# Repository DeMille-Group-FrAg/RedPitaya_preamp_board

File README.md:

Schematics for a simple amplifier pcb to step Red Pitaya output voltage from 0--1V or 0--2V up to 0--5V (or other gain, if so desired). See the documentation section in https://github.com/DeMille-Group-FrAg/TransferInterferometer.

Designed by John Dewhurst in February 2023 for FrAg.

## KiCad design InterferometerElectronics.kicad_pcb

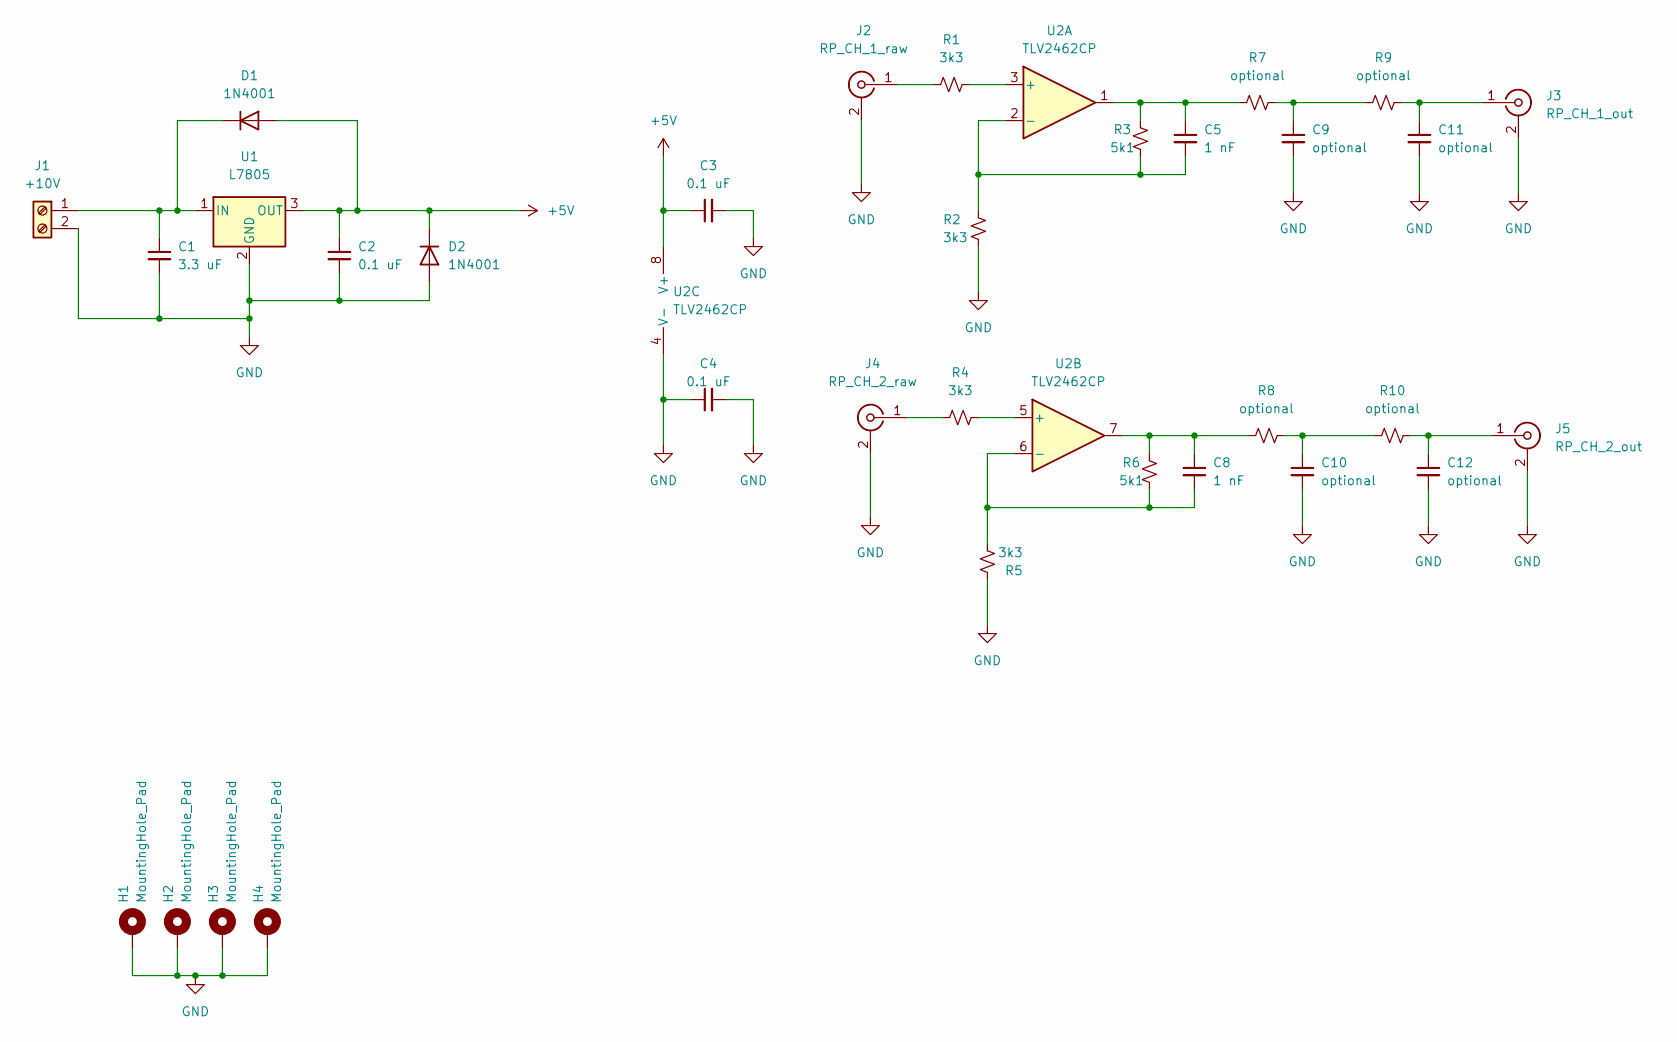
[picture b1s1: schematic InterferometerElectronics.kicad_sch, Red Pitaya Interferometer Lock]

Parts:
C1: 3.3 uF; C_Disc_D7.5mm_W5.0mm_P7.50mm
C2, C3, C4: 0.1 uF; C_Disc_D7.5mm_W5.0mm_P7.50mm
C5, C8: 1 nF; C_Disc_D7.5mm_W5.0mm_P7.50mm
C9, C10, C11, C12: optional; C_Disc_D7.5mm_W5.0mm_P7.50mm
D1, D2: 1N4001; D_DO-41_SOD81_P10.16mm_Horizontal
H1, H2, H3, H4: MountingHole_Pad; MountingHole_3mm_Pad_Via
J1: +10V; PhoenixContact_MCV_1,5_2-G-5.08_1x02_P5.08mm_Vertical
J2: RP_CH_1_raw; SMA_Amphenol_132134-16_Vertical
J3: RP_CH_1_out; SMA_Amphenol_132134-16_Vertical
J4: RP_CH_2_raw; SMA_Amphenol_132134-16_Vertical
J5: RP_CH_2_out; SMA_Amphenol_132134-16_Vertical
R1, R2, R4, R5: 3k3; R_Axial_DIN0207_L6.3mm_D2.5mm_P10.16mm_Horizontal
R3, R6: 5k1; R_Axial_DIN0207_L6.3mm_D2.5mm_P10.16mm_Horizontal
R7, R8, R9, R10: optional; R_Axial_DIN0207_L6.3mm_D2.5mm_P10.16mm_Horizontal
U1: L7805; TO-220-3_Horizontal_TabDown
U2: TLV2462CP; DIP-8_W7.62mm_Socket

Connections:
+5V: C2.1, C3.1, D1.2 (A), D2.1 (K), U1.3 (OUT), U2.8 (V+)
GND: C1.2, C2.2, C3.2, C4.1, C4.2, C9.2, C10.2, C11.2, C12.2, D2.2 (A), H1.1, H2.1, H3.1, H4.1, J1.2, J2.2 (Ext), J3.2 (Ext), J4.2 (Ext), J5.2 (Ext), R2.2, R5.1, U1.2 (GND), U2.4 (V-)
unnamed: C1.1, D1.1 (K), J1.1, U1.1 (IN)
unnamed: C5.1, R3.1, R7.1, U2.1
unnamed: C5.2, R2.1, R3.2, U2.2 (-)
unnamed: C8.1, R6.1, R8.1, U2.7
unnamed: C8.2, R5.2, R6.2, U2.6 (-)
unnamed: C9.1, R7.2, R9.1
unnamed: C10.1, R8.2, R10.1
unnamed: C11.1, J3.1 (In), R9.2
unnamed: C12.1, J5.1 (In), R10.2
unnamed: J2.1 (In), R1.1
unnamed: J4.1 (In), R4.1
unnamed: R1.2, U2.3 (+)
unnamed: R4.2, U2.5 (+)

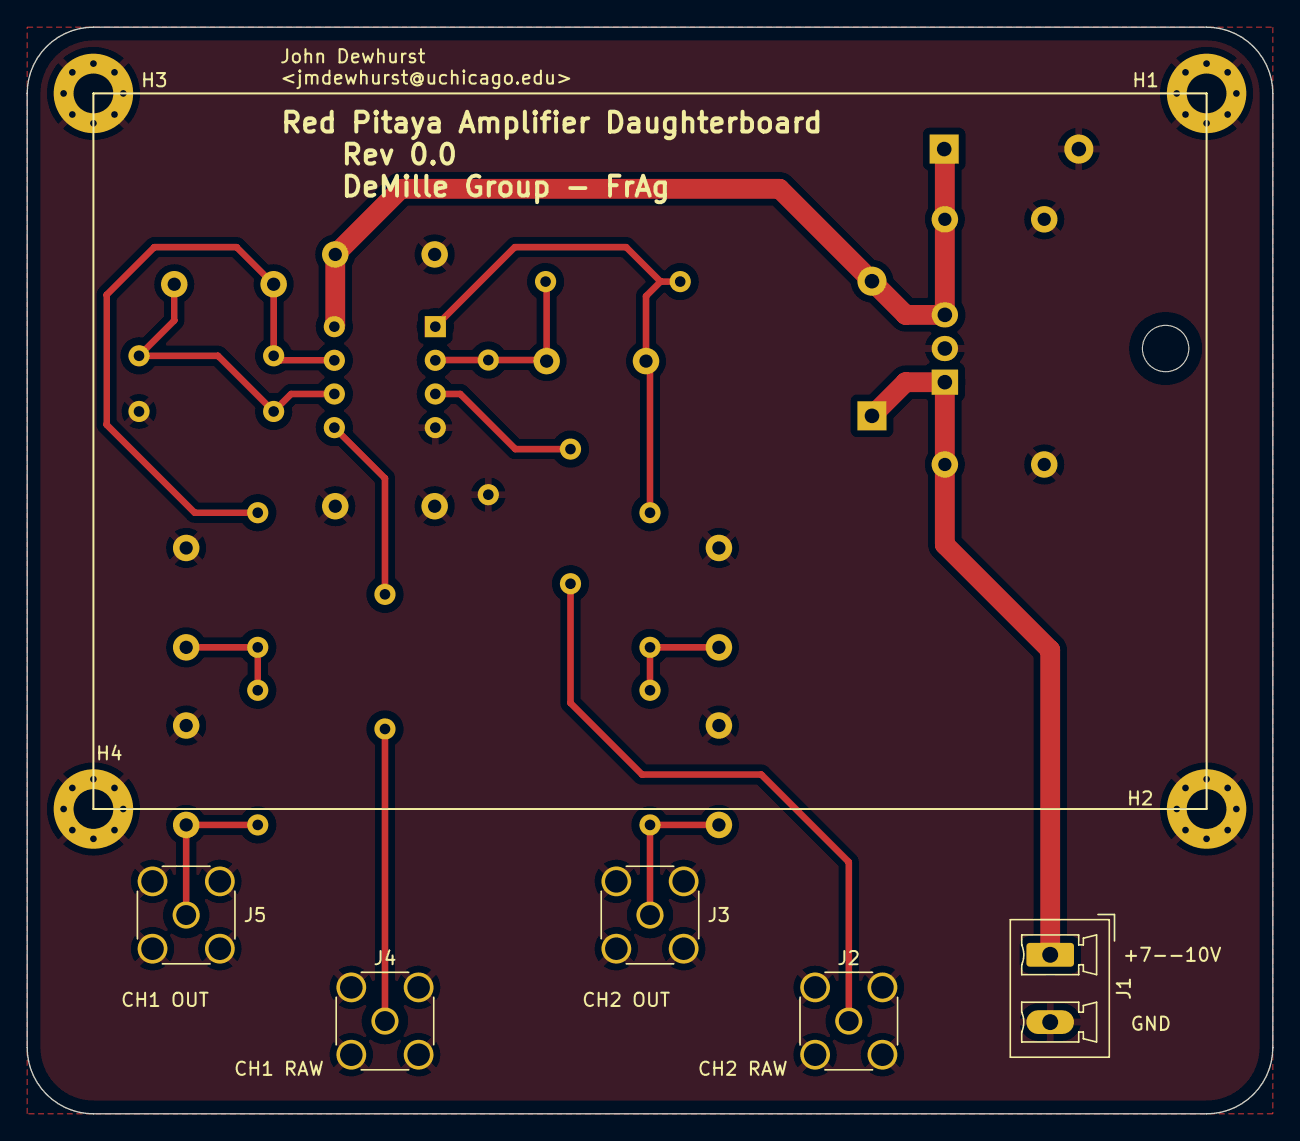
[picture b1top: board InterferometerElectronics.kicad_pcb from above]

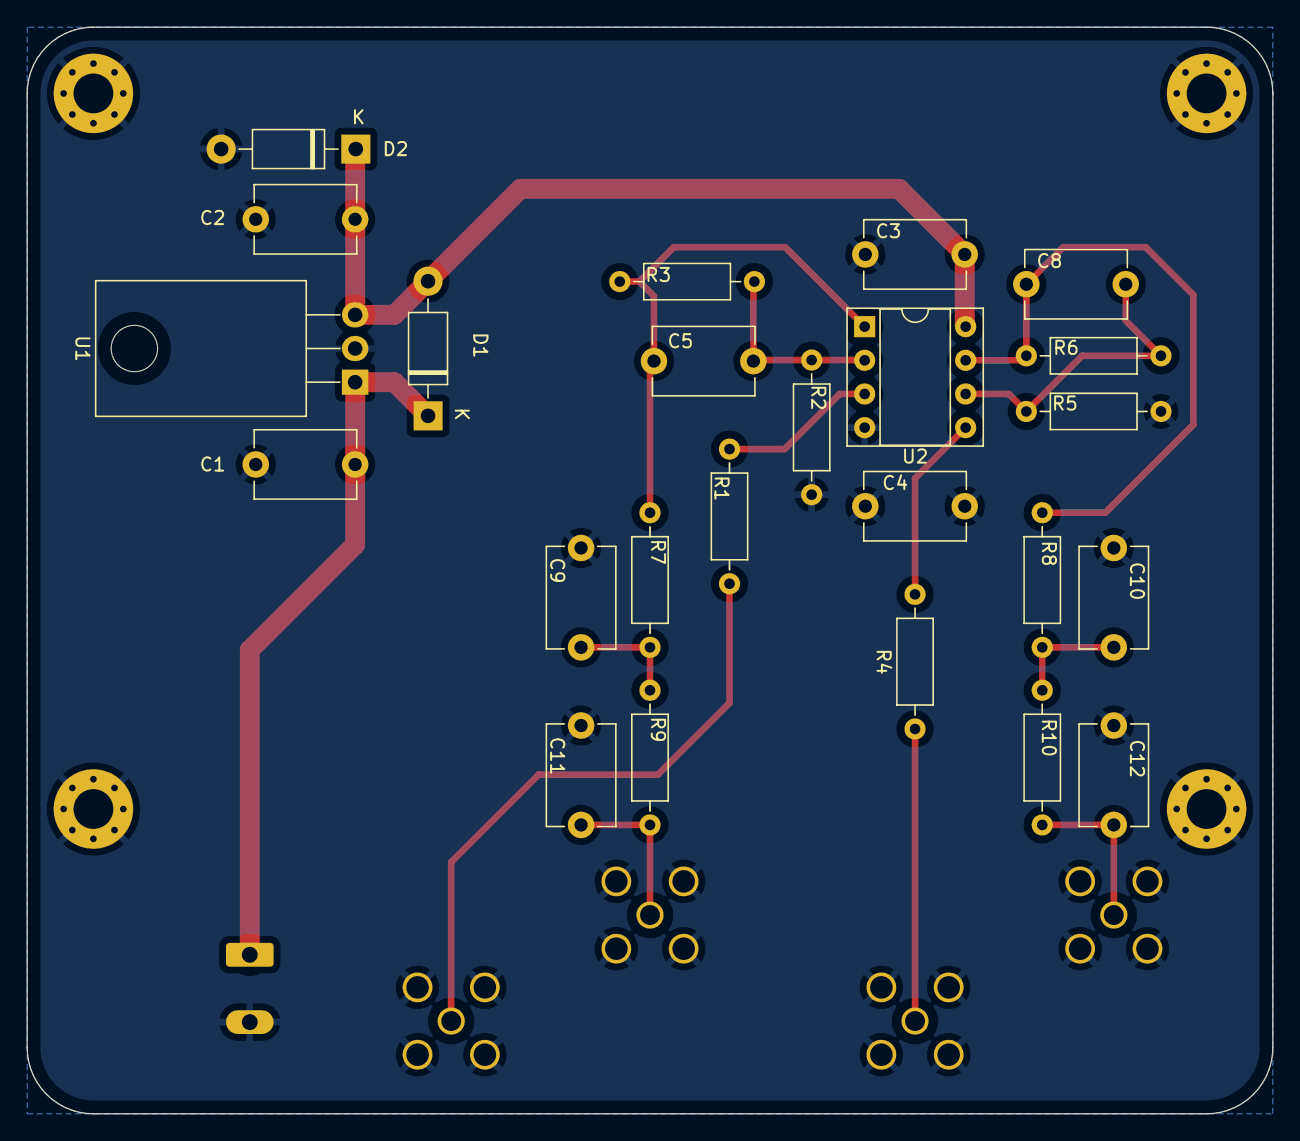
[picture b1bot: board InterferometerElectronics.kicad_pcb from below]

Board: 2 copper layers, 94.0 x 82.0 mm, 33 parts (24 on the bottom side), 15 nets.

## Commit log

2023-06-13 added minimal readme
